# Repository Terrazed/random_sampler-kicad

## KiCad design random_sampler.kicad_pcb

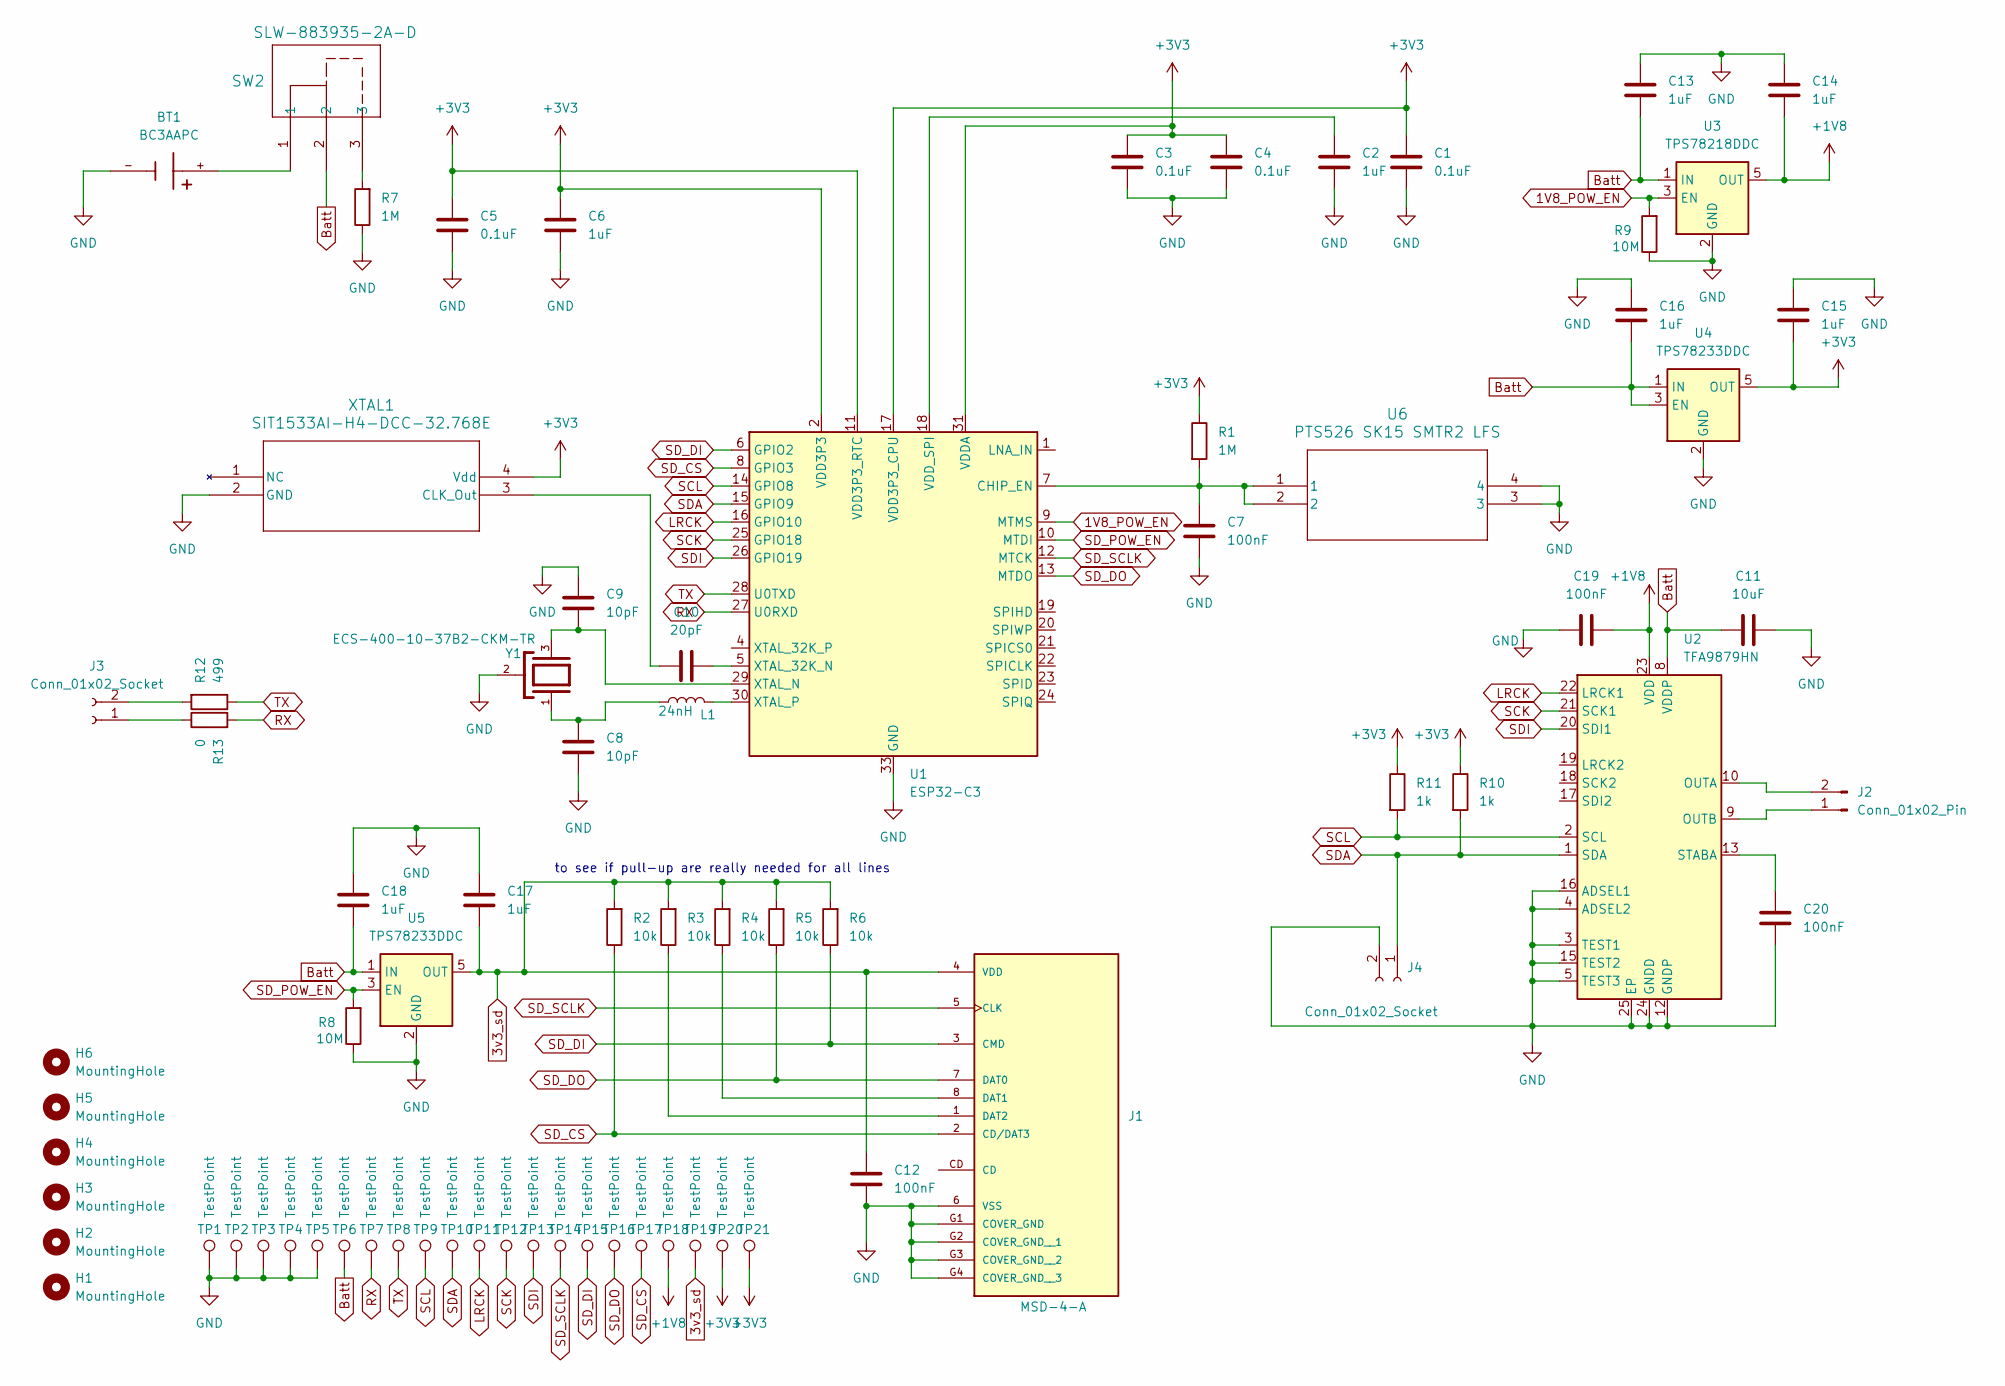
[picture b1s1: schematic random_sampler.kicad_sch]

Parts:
BT1: BC3AAPC; BAT_BC3AAPC; PARTREV J
C1, C3, C4, C5: 0.1uF; C_0805_2012Metric_Pad1.18x1.45mm_HandSolder
C2, C6, C13, C14, C15, C16, C17, C18: 1uF; C_0805_2012Metric_Pad1.18x1.45mm_HandSolder
C7, C12, C19, C20: 100nF; C_0805_2012Metric_Pad1.18x1.45mm_HandSolder
C8, C9: 10pF; C_0805_2012Metric_Pad1.18x1.45mm_HandSolder
C10: 20pF; C_0805_2012Metric_Pad1.18x1.45mm_HandSolder
C11: 10uF; C_0805_2012Metric_Pad1.18x1.45mm_HandSolder
H1, H2, H3, H4, H5, H6: MountingHole; MountingHole_3.2mm_M3
J1: MSD-4-A; CUI_MSD-4-A; PARTREV 1.0
J2: Conn_01x02_Pin; PinHeader_1x02_P2.54mm_Vertical
J3, J4: Conn_01x02_Socket; PinSocket_1x02_P2.54mm_Horizontal
L1: 24nH; L_0805_2012Metric_Pad1.15x1.40mm_HandSolder
R1, R7: 1M; R_0805_2012Metric_Pad1.20x1.40mm_HandSolder
R2, R3, R4, R5, R6: 10k; R_0805_2012Metric_Pad1.20x1.40mm_HandSolder
R8, R9: 10M; R_0805_2012Metric_Pad1.20x1.40mm_HandSolder
R10, R11: 1k; R_0805_2012Metric_Pad1.20x1.40mm_HandSolder
R12: 499; R_0805_2012Metric_Pad1.20x1.40mm_HandSolder
R13: 0; R_0805_2012Metric_Pad1.20x1.40mm_HandSolder
SW2: SLW-883935-2A-D; PinSocket_1x03_P2.54mm_Vertical
TP1, TP2, TP3, TP4, TP5, TP6, TP7, TP8, TP9, TP10, TP11, TP12, TP13, TP14, TP15, TP16, TP17, TP18, TP19, TP20, TP21: TestPoint; TestPoint_THTPad_D2.0mm_Drill1.0mm
U1: ESP32-C3; QFN-32-1EP_5x5mm_P0.5mm_EP3.7x3.7mm
U2: TFA9879HN; HVQFN-24-1EP_4x4mm_P0.5mm_EP2.6x2.6mm_ThermalVias
U3: TPS78218DDC; SOT-23-5
U4, U5: TPS78233DDC; SOT-23-5
U6: PTS526 SK15 SMTR2 LFS; SMT_FS
XTAL1: SIT1533AI-H4-DCC-32.768E; XTAL4_SiT1533_SIT
Y1: ECS-400-10-37B2-CKM-TR; XTAL_ECS-400-10-37B2-CKM-TR; PARTREV 2021

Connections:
1V8_POW_EN: R9.2, U1.9 (MTMS), U3.3 (EN)
3v3_sd: C12.1, C17.2, J1.4 (VDD), R2.2, R3.2, R4.2, R5.2, R6.2, TP19.1, U5.5 (OUT)
+1V8: C14.2, C19.2, TP18.1, U2.23 (VDD), U3.5 (OUT)
+3V3: C1.1, C3.1, C4.1, C5.1, C6.1, C15.2, R1.1, R10.1, R11.1, TP20.1, TP21.1, U1.2 (VDD3P3), U1.3 (VDD3P3), U1.11 (VDD3P3_RTC), U1.17 (VDD3P3_CPU), U1.31 (VDDA), U1.32 (VDDA), U4.5 (OUT), XTAL1.4 (Vdd)
Batt: C11.1, C13.2, C16.2, C18.2, SW2.2, TP6.1, U2.7 (VDDP), U2.8 (VDDP), U3.1 (IN), U4.1 (IN), U4.3 (EN), U5.1 (IN)
GND: BT1.-, C1.2, C2.2, C3.2, C4.2, C5.2, C6.2, C7.2, C8.2, C9.2, C11.2, C12.2, C13.1, C14.1, C15.1, C16.1, C17.1, C18.1, C19.1, C20.1, J1.6 (VSS), J1.G1 (COVER_GND), J1.G2 (COVER_GND__1), J1.G3 (COVER_GND__2), J1.G4 (COVER_GND__3), J4.2, R7.1, R8.1, R9.1, TP1.1, TP2.1, TP3.1, TP4.1, TP5.1, U1.33 (GND), U2.3 (TEST1), U2.4 (ADSEL2), U2.5 (TEST3), U2.11 (GNDP), U2.12 (GNDP), U2.15 (TEST2), U2.16 (ADSEL1), U2.24 (GNDD), U2.25 (EP), U3.2 (GND), U3.4 (GND), U4.2 (GND), U4.4 (GND), U5.2 (GND), U5.4 (GND), U6.3, U6.4, XTAL1.2 (GND), Y1.2
LRCK: TP11.1, U1.16 (GPIO10), U2.22 (LRCK1)
unnamed: BT1.+, SW2.1
unnamed: C8.1, L1.1, Y1.1
unnamed: J1.8 (DAT1), R4.1
unnamed: J1.1 (DAT2), R3.1
unnamed: J2.1, U2.9 (OUTB)
unnamed: J2.2, U2.10 (OUTA)
unnamed: J3.1, R13.1
unnamed: J3.2, R12.2
unnamed: R7.2, SW2.3
unnamed: C7.1, R1.2, U1.7 (CHIP_EN), U6.1, U6.2
unnamed: C2.1, U1.18 (VDD_SPI)
unnamed: C10.1, U1.5 (XTAL_32K_N)
unnamed: C9.1, U1.29 (XTAL_N), Y1.3
unnamed: L1.2, U1.30 (XTAL_P)
unnamed: C20.2, U2.13 (STABA)
unnamed: C10.2, XTAL1.3 (CLK_Out)
RX: R13.2, TP7.1, U1.27 (U0RXD)
SCK: TP12.1, U1.25 (GPIO18), U2.21 (SCK1)
SCL: R11.2, TP9.1, U1.14 (GPIO8), U2.2 (SCL)
SDA: J4.1, R10.2, TP10.1, U1.15 (GPIO9), U2.1 (SDA)
SDI: TP13.1, U1.26 (GPIO19), U2.20 (SDI1)
SD_CS: J1.2 (CD/DAT3), R2.1, TP17.1, U1.8 (GPIO3)
SD_DI: J1.3 (CMD), R6.1, TP15.1, U1.6 (GPIO2)
SD_DO: J1.7 (DAT0), R5.1, TP16.1, U1.13 (MTDO)
SD_POW_EN: R8.2, U1.10 (MTDI), U5.3 (EN)
SD_SCLK: J1.5 (CLK), TP14.1, U1.12 (MTCK)
TX: R12.1, TP8.1, U1.28 (U0TXD)

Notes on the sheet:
to see if pull-up are really needed for all lines

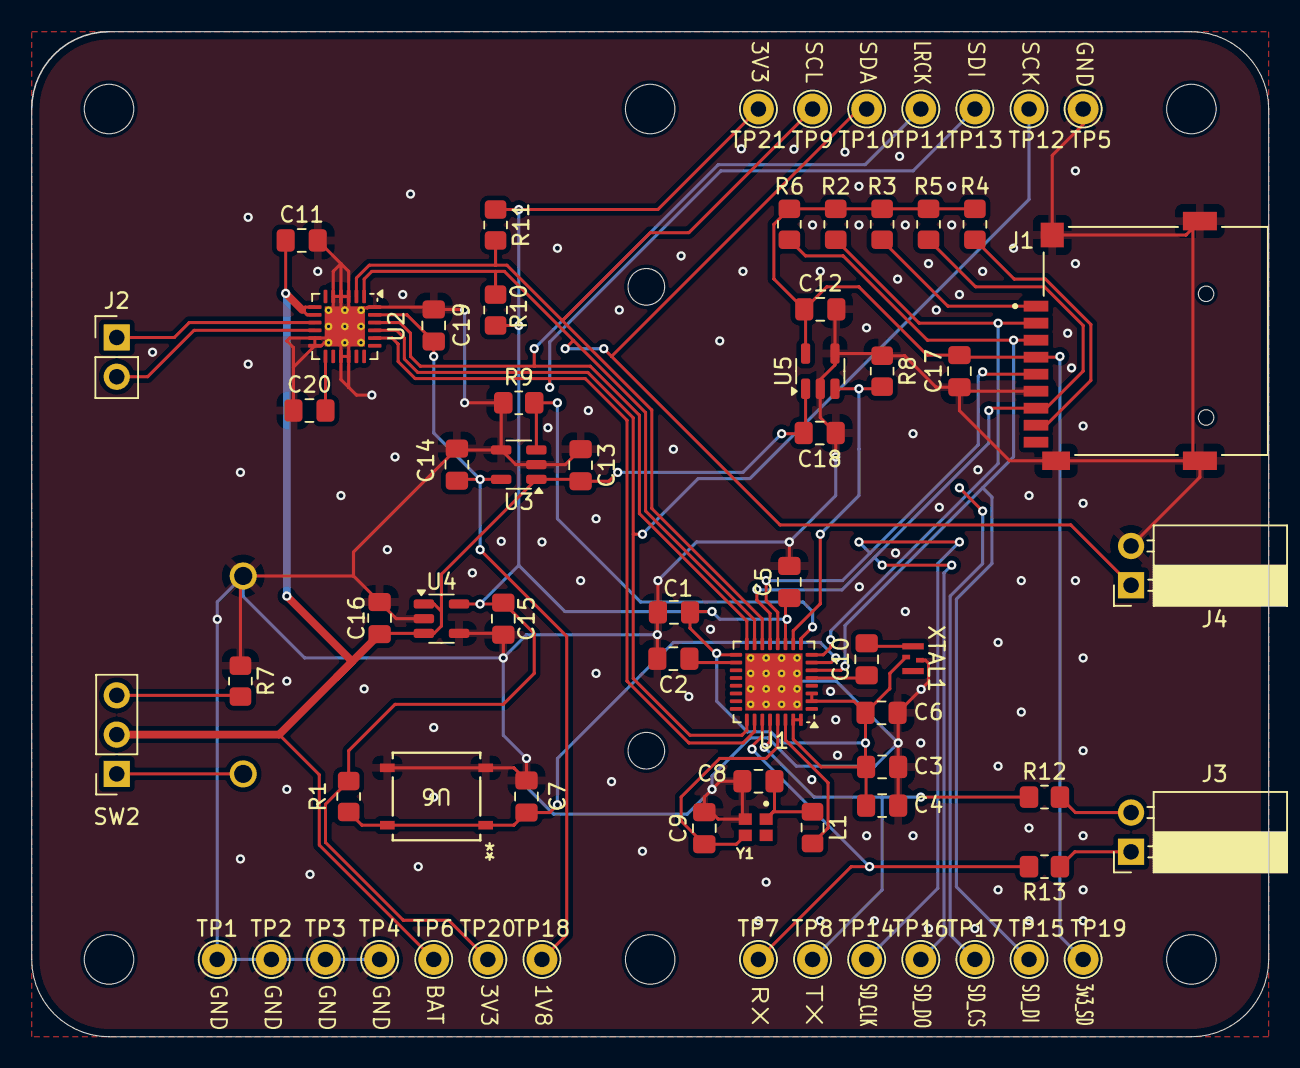
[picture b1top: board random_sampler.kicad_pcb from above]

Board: 2 copper layers, 80.0 x 65.0 mm, 75 parts (1 on the bottom side), 34 nets.

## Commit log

2025-04-25 init git
